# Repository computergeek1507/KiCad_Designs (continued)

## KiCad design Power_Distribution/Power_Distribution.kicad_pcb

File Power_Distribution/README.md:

# Copyright and Disclaimer
Copyright: Scott Hanson

This documentation describes Open Hardware and is licensed under the CERN OHL v. 1.2.

You may redistribute and modify this documentation under the terms of the CERN OHL v.1.2. (http://ohwr.org/cernohl). This documentation is distributed WITHOUT ANY EXPRESS OR IMPLIED WARRANTY, INCLUDING OF MERCHANTABILITY, SATISFACTORY QUALITY AND FITNESS FOR A PARTICULAR PURPOSE. Please see the CERN OHL v.1.2 for applicable conditions

# Power Distribution

Fused Power Distribution Board with Screw Terminals.

# BOM
| Component | Qty | Description              | Digi-Key PN  | Manufacturer             | Manufacturer PN |
|-----------|-----|--------------------------|--------------|--------------------------|-----------------|
| J1,J2     |  2  | TERM BLK 8P Side 5.08MM  | 609-3942-ND  | Amphenol Anytek          | VI0821550000G   |
| F1 - F8   |  8  | FUSE HOLDER BLADE 30A    | 36-3544-2-ND | Keystone Electronics     | 3544-2          |
| F1 - F8   |  8  | FUSE AUTO 5A BLADE MINI  | F989-ND      | Littelfuse               | 0297005.WXNV    |
| TB1       |  1  | CONN BARRIER STRIP 0.374 | ED2953-ND    | On Shore Technology Inc. | OSTYK51102030   |

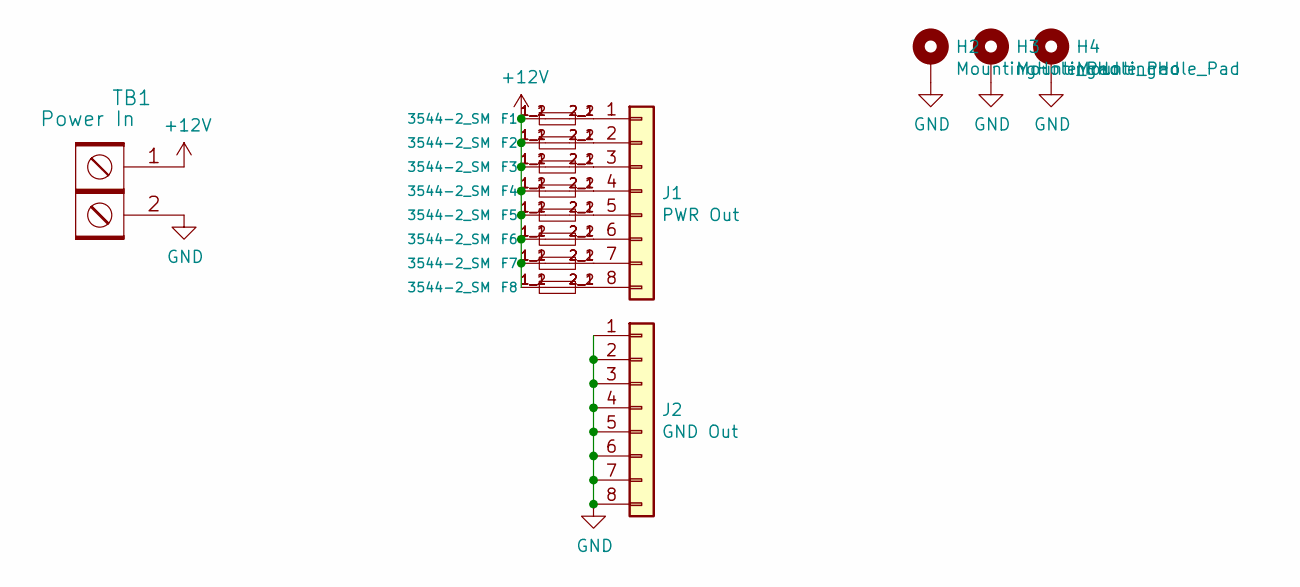
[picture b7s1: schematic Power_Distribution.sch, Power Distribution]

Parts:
F1, F2, F3, F4, F5, F6, F7, F8: 3544-2_SM; FUSE_3544-2; Digi-Key PN 36-3544-2-ND
H2, H3, H4: MountingHole_Pad; MountingHole_3.5mm_Pad_Via
J1: PWR Out; PhoenixContact_MCV_1,5_8-G-5.08_1x08_P5.08mm_Vertical; Digi-Key PN 609-3942-ND
J2: GND Out; PhoenixContact_MCV_1,5_8-G-5.08_1x08_P5.08mm_Vertical; Digi-Key PN 609-3942-ND
TB1: Power In; BARRIER_BLOCK_1ROW_2POS_P9.5MM; Digi-Key PN ED2953-ND

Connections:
+12V: F1.1_1 (1), F1.1_2 (1), F2.1_1 (1), F2.1_2 (1), F3.1_1 (1), F3.1_2 (1), F4.1_1 (1), F4.1_2 (1), F5.1_1 (1), F5.1_2 (1), F6.1_1 (1), F6.1_2 (1), F7.1_1 (1), F7.1_2 (1), F8.1_1 (1), F8.1_2 (1), TB1.1
GND: H2.1, H3.1, H4.1, J2.1, J2.2, J2.3, J2.4, J2.5, J2.6, J2.7, J2.8, TB1.2
unnamed: F1.2_1 (2), F1.2_2 (2), J1.1
unnamed: F2.2_1 (2), F2.2_2 (2), J1.2
unnamed: F3.2_1 (2), F3.2_2 (2), J1.3
unnamed: F4.2_1 (2), F4.2_2 (2), J1.4
unnamed: F5.2_1 (2), F5.2_2 (2), J1.5
unnamed: F6.2_1 (2), F6.2_2 (2), J1.6
unnamed: F7.2_1 (2), F7.2_2 (2), J1.7
unnamed: F8.2_1 (2), F8.2_2 (2), J1.8

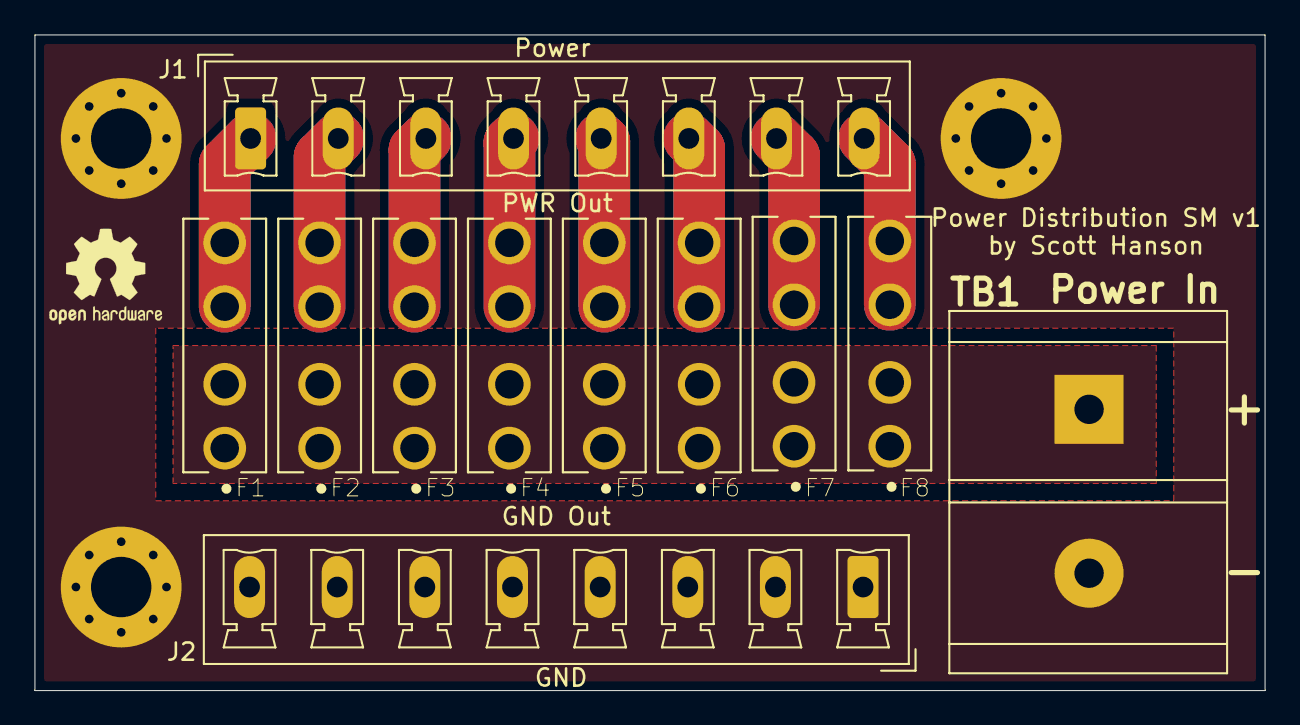
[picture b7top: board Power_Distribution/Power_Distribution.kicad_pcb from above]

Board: 2 copper layers, 71.3 x 38.0 mm, 14 parts (0 on the bottom side), 10 nets.

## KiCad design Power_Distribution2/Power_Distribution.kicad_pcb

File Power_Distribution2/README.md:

# Copyright and Disclaimer
Copyright: Scott Hanson

This documentation describes Open Hardware and is licensed under the CERN OHL v. 1.2.

You may redistribute and modify this documentation under the terms of the CERN OHL v.1.2. (http://ohwr.org/cernohl). This documentation is distributed WITHOUT ANY EXPRESS OR IMPLIED WARRANTY, INCLUDING OF MERCHANTABILITY, SATISFACTORY QUALITY AND FITNESS FOR A PARTICULAR PURPOSE. Please see the CERN OHL v.1.2 for applicable conditions

# Power Distribution

Fused Power Distribution Board with 8 Phoenic Terminals.

# BOM
| Component | Qty | Description                | Digi-Key PN     | Manufacturer               | Manufacturer PN |
|-----------|-----|----------------------------|-----------------|----------------------------|-----------------|
| D1        |  1  | LED GREEN DIFFUSED         | 754-1217-ND     | Kingbright                 | WP3A8GD         |
| J1 - J8   |  8  | TERM BLOCK 2POS 3.5MM      | 277-5733-ND     | Phoenix Contact            | 1843606         |
| J1 - J8   |  8  | TERM BLOCK PLUG 2POS 3.5MM | ED10554-ND      | On Shore Technology Inc.   | OSTTJ0211530    |
| F1 - F8   |  8  | FUSE HOLDER BLADE 30A      | 36-3544-2-ND    | Keystone Electronics       | 3544-2          |
| F1 - F8   |  8  | FUSE AUTO 5A BLADE MINI    | F989-ND         | Littelfuse                 | 0297005.WXNV    |
| R1        |  1  | RES 1K OHM 1/4W 5%         | CF14JT1K00CT-ND | Stackpole Electronics Inc. | CF14JT1K00      |
| TB1       |  1  | CONN BARRIER STRIP 0.374   | ED2953-ND       | On Shore Technology Inc.   | OSTYK51102030   |

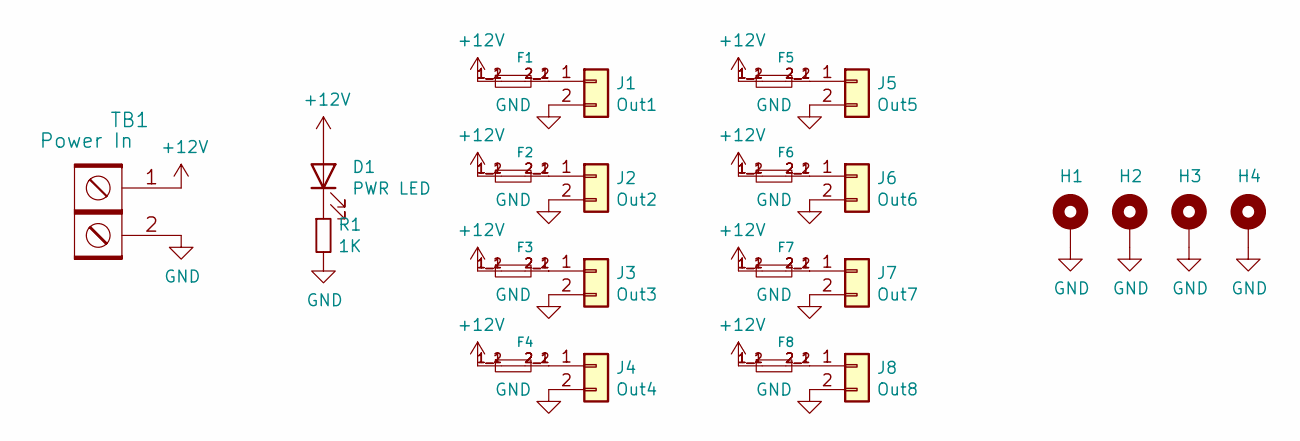
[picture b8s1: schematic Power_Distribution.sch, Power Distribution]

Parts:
D1: PWR LED; LED_D3.0mm_Clear; Digi-Key_PN 754-1217-ND
F1, F2, F3, F4, F5, F6, F7, F8: 3544-2_SM; FUSE_3544-2; Digi-Key_PN 36-3544-2-ND
H1, H2, H3, H4: MountingHole_Pad; MountingHole_3.5mm_Pad_Via
J1: Out1; PhoenixContact_MCV_1,5_2-G-3.81_1x02_P3.81mm_Vertical; Digi-Key_PN 277-5733-ND/ED10554-ND
J2: Out2; PhoenixContact_MCV_1,5_2-G-3.81_1x02_P3.81mm_Vertical; Digi-Key_PN 277-5733-ND/ED10554-ND
J3: Out3; PhoenixContact_MCV_1,5_2-G-3.81_1x02_P3.81mm_Vertical; Digi-Key_PN 277-5733-ND/ED10554-ND
J4: Out4; PhoenixContact_MCV_1,5_2-G-3.81_1x02_P3.81mm_Vertical; Digi-Key_PN 277-5733-ND/ED10554-ND
J5: Out5; PhoenixContact_MCV_1,5_2-G-3.81_1x02_P3.81mm_Vertical; Digi-Key_PN 277-5733-ND/ED10554-ND
J6: Out6; PhoenixContact_MCV_1,5_2-G-3.81_1x02_P3.81mm_Vertical; Digi-Key_PN 277-5733-ND/ED10554-ND
J7: Out7; PhoenixContact_MCV_1,5_2-G-3.81_1x02_P3.81mm_Vertical; Digi-Key_PN 277-5733-ND/ED10554-ND
J8: Out8; PhoenixContact_MCV_1,5_2-G-3.81_1x02_P3.81mm_Vertical; Digi-Key_PN 277-5733-ND/ED10554-ND
R1: 1K; R_Axial_DIN0207_L6.3mm_D2.5mm_P7.62mm_Horizontal; Digi-Key_PN CF14JT1K00CT-ND
TB1: Power In; BARRIER_BLOCK_1ROW_2POS_P9.5MM; Digi-Key_PN ED2953-ND

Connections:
+12V: D1.2 (A), F1.1_1 (1), F1.1_2 (1), F2.1_1 (1), F2.1_2 (1), F3.1_1 (1), F3.1_2 (1), F4.1_1 (1), F4.1_2 (1), F5.1_1 (1), F5.1_2 (1), F6.1_1 (1), F6.1_2 (1), F7.1_1 (1), F7.1_2 (1), F8.1_1 (1), F8.1_2 (1), TB1.1
GND: H1.1, H2.1, H3.1, H4.1, J1.2, J2.2, J3.2, J4.2, J5.2, J6.2, J7.2, J8.2, R1.2, TB1.2
unnamed: D1.1 (K), R1.1
unnamed: F1.2_1 (2), F1.2_2 (2), J1.1
unnamed: F2.2_1 (2), F2.2_2 (2), J2.1
unnamed: F3.2_1 (2), F3.2_2 (2), J3.1
unnamed: F4.2_1 (2), F4.2_2 (2), J4.1
unnamed: F5.2_1 (2), F5.2_2 (2), J5.1
unnamed: F6.2_1 (2), F6.2_2 (2), J6.1
unnamed: F7.2_1 (2), F7.2_2 (2), J7.1
unnamed: F8.2_1 (2), F8.2_2 (2), J8.1

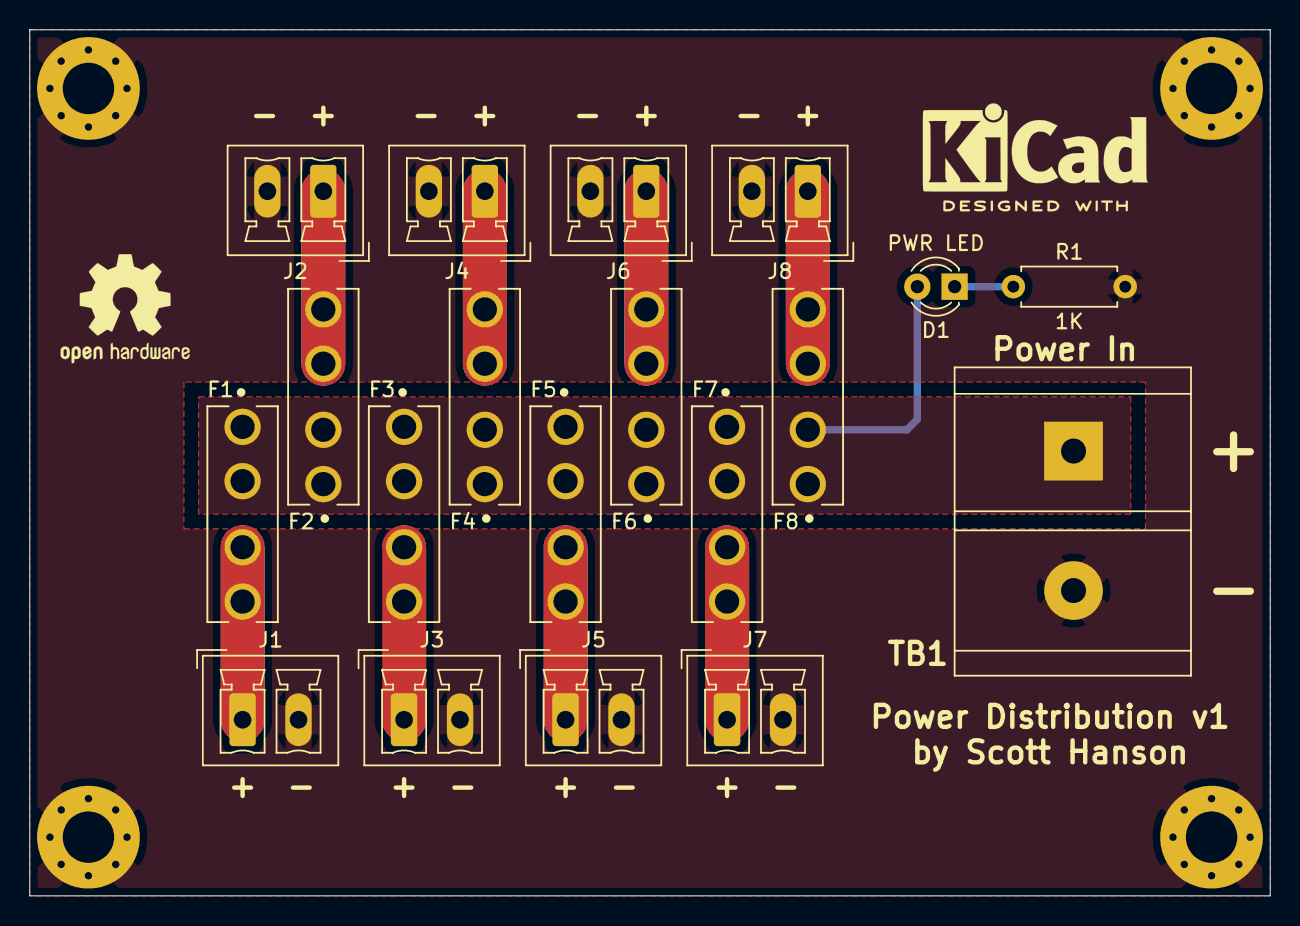
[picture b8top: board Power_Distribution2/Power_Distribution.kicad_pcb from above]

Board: 2 copper layers, 84.5 x 59.0 mm, 23 parts (0 on the bottom side), 11 nets.
